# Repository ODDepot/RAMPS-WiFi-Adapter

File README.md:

The RAMPS WiFi Adapter provides wireless networking for RepRap's RAMPS (Arduino Mega Pololu Shield) controller.

### News

#### 9/4/2013
Version 0.2 has been tested and is functional. Further work on setup.ino and setup.py is needed for a friendly configuration process. Higher baudrates may be achieved but have not been fully tested.

#### 6/19/2013
Version 0.2 is ready to be ordered and tested. The LM358DMR2G is replacing the TLV2452CDGKR and voltage dividers are being added along with a pullup and pulldown resistor. The first version has some errors. Overdriving the TLV2452CDGKR inputs at 5V with 3.3V supply is not possible. Replacing it with a LM358DMR2G works, however, a pullup resistor for RESET and a pulldown resistor for GPIO9 on the RN-171 is needed whenever jumpers are not connected. Besides these issues, Version 0.1 is able to connect and send data. The antenna appears very capable.

#### 5/13/2013
Boards for the first version have been ordered and testing will begin soon.

### Setup

#### Using Marlin firmware and Pronterface host software
Make sure the RAMPS WiFi Adapter is installed correctly on RAMPS and the Reset and Default pin jumpers are in place. Upload setup.ino to the Arduino Mega with your custom settings. Observe output from the RN171 (WiFi module onboard the adapter) with the Arduino IDE Serial Monitor. If the RN171 successful assoicates with your wireless network, the RN171 should provide an IP Address and the only LED blinking should be green. Verify this by checking your router. Also, you may want to configure your router for Static DHCP so that it always leases the same IP Address for the same MAC Address (on the RN171).

In Configuration.h of Marlin, change '#define SERIAL_PORT 0' to '#define SERIAL_PORT 2' and change '#define BAUDRATE 250000' to '#define BAUDRATE 9600', then upload. Remove the Reset and Default pin jumpers and reset RAMPS. Wait a few seconds. In Pronterface, type [IP Address]:2000 into the 'Port' bar (for example, 192.168.1.100:2000), then connect.

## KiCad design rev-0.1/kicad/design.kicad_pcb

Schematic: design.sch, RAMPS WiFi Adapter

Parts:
AE1: ANTENNA
C1: T491A475K016AT
D1: APT2012SGC
D2: APT2012YC
D3: APT2012EC
P1: AUX-4_INTERFACE
P2: I2C_INTERFACE
P3: ENABLE_JUMPERS
R1, R2, R3: CR0805-FX-2400ELF
U1: RN-171
U2: TXB0106PWR
U3: TLV2452CDGKR
U4: TC1262-3.3VDB

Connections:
/3.3V: C1.1, U1.10 (VDD_3.3V), U1.34 (VDD_3.3V_RF), U1.49 (VDD_BATT), U2.2 (VCCA), U2.8 (OE), U3.8 (VDD), U4.3 (VOUT)
/5V: P1.1, P2.1, U2.15 (VCCB), U4.1 (VIN)
/DFLT3.3: U1.4 (GPIO9), U3.6 (2IN-), U3.7 (2OUT)
/DFLT5: P1.15, P3.3 (DFLT)
/DFLT_EN: P3.4 (DFLT_EN), U3.5 (2IN+)
/RST3.3: U1.40 (RESET), U3.1 (1OUT), U3.2 (1IN-)
/RST5: P1.16, P3.1 (RST)
/RST_EN: P3.2 (RST_EN), U3.3 (1IN+)
/RX3.3: U1.45 (UART_RX), U2.1 (A1)
/RX5: P1.18, U2.16 (B1)
/TX3.3: U1.46 (UART_TX), U2.3 (A2)
/TX5: P1.17, U2.14 (B2)
GND: C1.2, P1.2, P2.2, R1.2, R2.2, R3.2, U1.1 (GND), U1.14 (GND), U1.20 (GND), U1.21 (GND), U1.22 (GND), U1.23 (GND), U1.25 (GND), U1.26 (GND), U1.27 (GND), U1.28 (GND), U1.39 (GND), U1.47 (GND), U2.9 (GND), U3.4 (GND), U4.2 (GND), U4.4 (GND)
unnamed: AE1.1, U1.24 (ANTENNA)
unnamed: D1.2 (CA), R1.1
unnamed: D2.1 (AN), U1.8 (GPIO5)
unnamed: D3.1 (AN), U1.7 (GPIO6)
unnamed: D1.1 (AN), U1.9 (GPIO4)
unnamed: D3.2 (CA), R3.1
unnamed: D2.2 (CA), R2.1

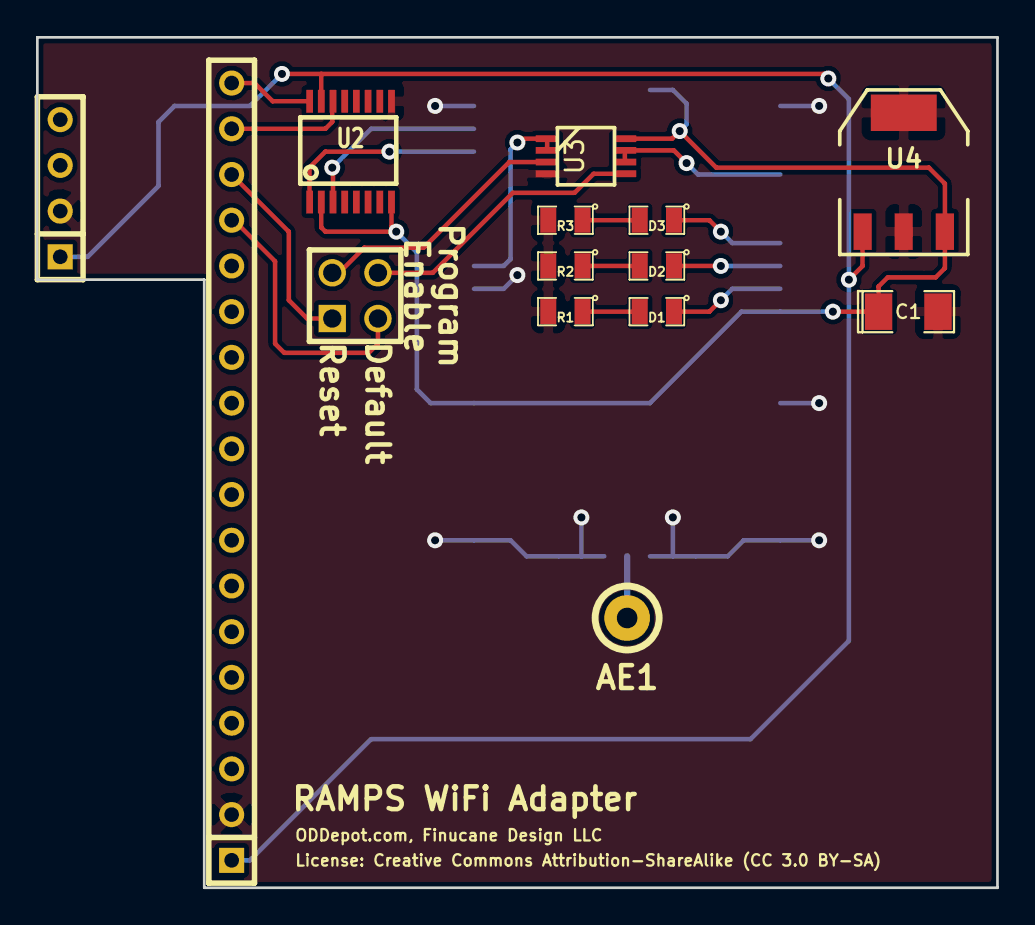
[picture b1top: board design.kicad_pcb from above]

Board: 2 copper layers, 53.3 x 47.2 mm, 15 parts (1 on the bottom side), 20 nets.

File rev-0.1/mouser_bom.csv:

part_number,quantity
517-9691020000DA,2
517-9612066404AR,1
517-9611046404AR,1
517-9611106404AR,2
652-CR0805FX-2400ELF,3
765-RN-171,1
595-TLV2452CDGKR,1
80-T491A475K016,1
579-TC1262-3.3VDB,1
595-TXB0106PWR,1
604-APT2012YC,1
604-APT2012SGC,1
604-APT2012EC,1

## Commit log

2013-05-13 Intial commit for rev-0.1, README.md, and LICENSE.md
2013-05-14 Create Mouser BOM
2013-06-07 Generate solder paste gerber files
2013-06-19 Adding rev-0.2 which corrects some errors with rev-0.1 (see README). Also adding some some tools (still a work in progress) for configuring the RN-171.
2013-06-19 Formatting README
2013-09-03 Changing R6,R8 to 4.7KOhm and R7,R9 to 9.1KOhm. Removing unused libraries from Eeschema. Updating and fixing some errors in BOM.
2013-09-04 Adding setup.ino as the main method for configuration, debug.ino for serial communication and manual configuration, and rescue.ino for a factory reset procedure. Fixing issues with comm.py and setup.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
2013-09-09 Modifying send_command() to append "\r\n", removing broken code in loop(), allowing configuration of baud rate, and cleaning up some comments.

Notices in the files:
rev-0.1/kicad/design.kicad_pcb:
License: Creative Commons Attribution-ShareAlike (CC 3.0 BY-SA)
